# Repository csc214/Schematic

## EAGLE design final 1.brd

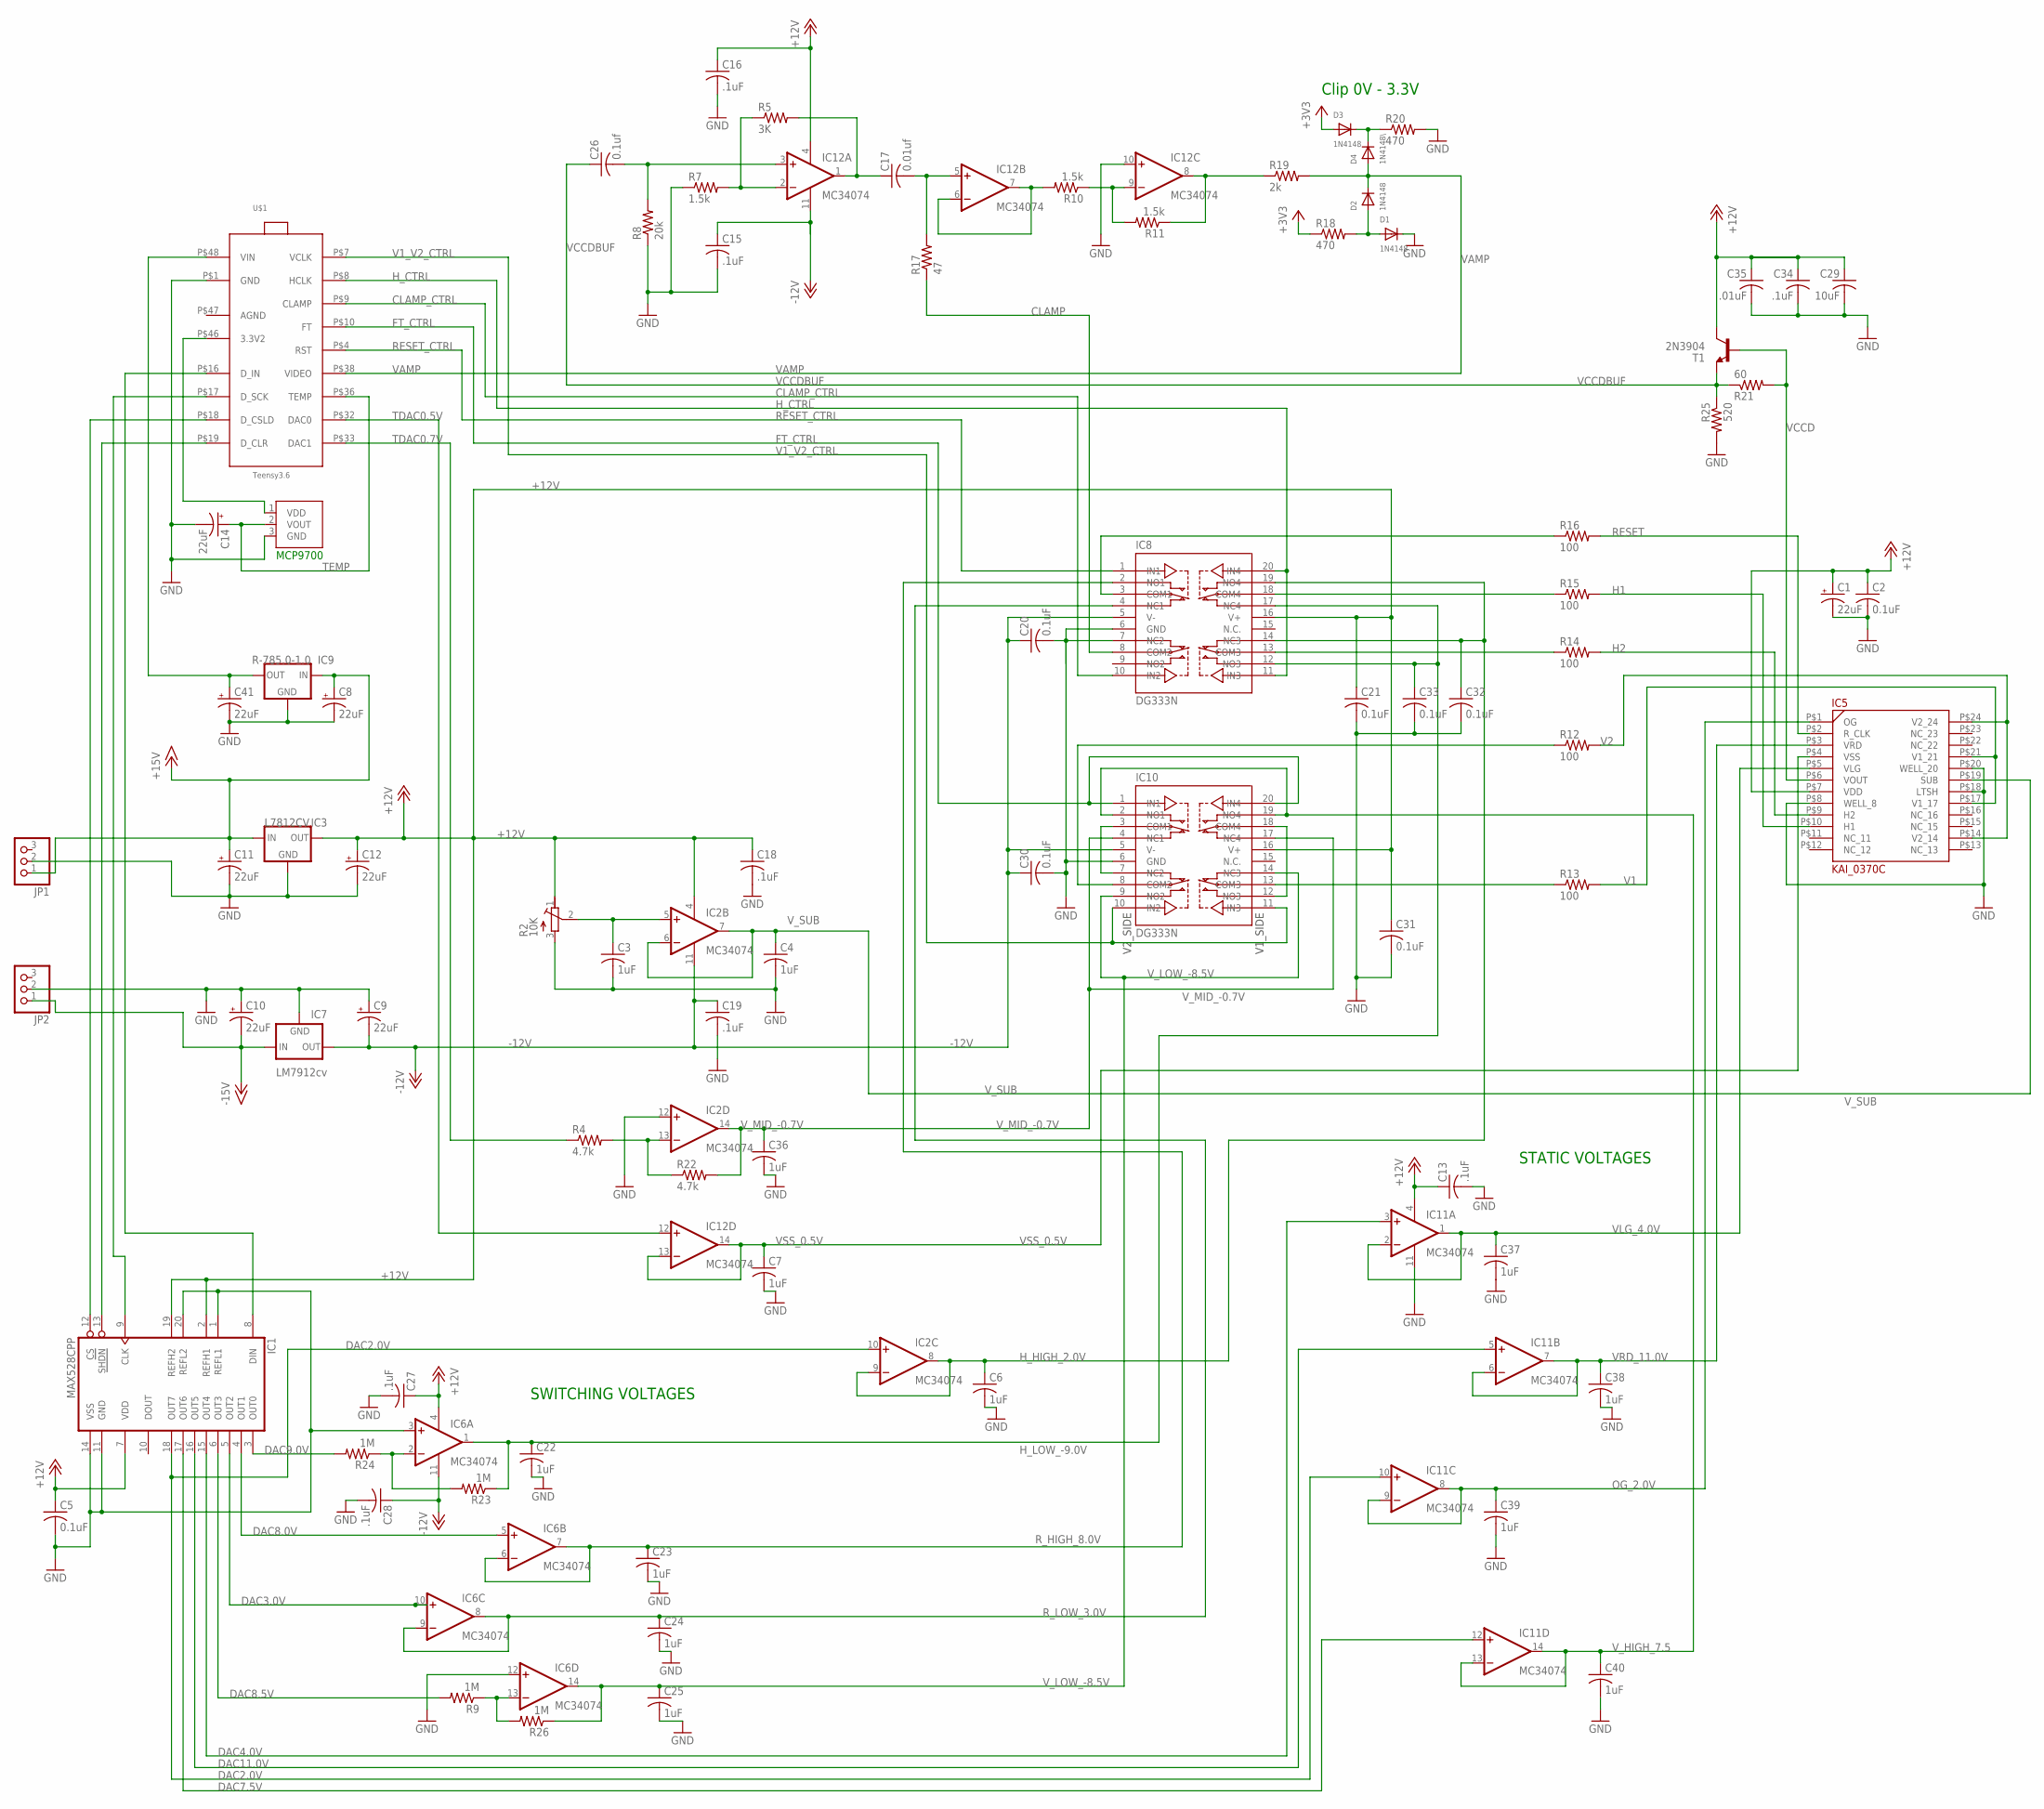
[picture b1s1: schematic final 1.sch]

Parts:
C1, C8, C9, C10, C11, C12, C14, C41: 22uF; SANYO-OSCON_F
C2, C5, C20, C21, C30, C31, C32, C33: 0.1uF; C050-050X075
C3, C4, C6, C7, C22, C23, C24, C25, C36, C37, C38, C39, C40: 1uF; C050-050X075
C13, C15, C16, C18, C19, C27, C28, C34: .1uF; C050-050X075
C17: 0.01uf; C050-050X075
C26: 0.1uf; C050-050X075
C29: 10uF; C050-050X075
C35: .01uF; C050-050X075
D1, D2, D3: 1N4148; DO-1N4148
D4: 1N4148\; DO-1N4148
IC1: MAX528CPP; DIL20
IC2, IC6, IC11, IC12: MC34074; DIL14
IC3: L7812CV; 78XXS
IC5: KAI_0370C; KAI-0370C
IC7: LM7912cv; 79XXS
IC8, IC10: DG333N; DIL20
IC9: R-785.0-1.0; SIP3
JP1, JP2: PINHD-1X3; 1X03
R2: 10K; RTRIM3006P
R4, R22: 4.7k; 0207/2V
R5: 3K; 0207/2V
R7, R10, R11: 1.5k; 0207/2V
R8: 20k; 0207/2V
R9, R23, R24, R26: 1M; 0207/2V
R12, R13, R14, R15, R16: 100; 0207/2V
R17: 47; 0207/2V
R18, R20: 470; 0207/2V
R19: 2k; 0207/2V
R21: 60; 0207/2V
R25: 520; 0207/2V
T1: 2N3904; TO92
U$1: TEENSY3.6LIMITED; DIL
U$2: MCP970XTO; TO92

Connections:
+3V3: D3.A, R18.1
+5V: C41.+, IC9.3 (OUT), U$1.P$48 (VIN)
+12V: C1.+, C2.1, C5.1, C12.+, C13.1, C16.1, C18.1, C21.1, C27.1, C29.1, C31.1, C34.1, C35.1, IC1.2 (REFH1), IC1.7 (VDD), IC1.19 (REFH2), IC2.4 (V+), IC3.OUT, IC5.P$7 (VDD), IC6.4 (V+), IC8.16 (V+), IC10.16 (V+), IC11.4 (V+), IC12.4 (V+), R2.1 (A), T1.1 (C)
+15V: C8.+, C11.+, IC3.IN, IC9.1 (IN), JP1.1
-12V: C9.-, C15.1, C19.1, C20.1, C28.1, C30.1, IC2.11 (V-), IC6.11 (V-), IC7.OUT, IC8.5 (V-), IC10.5 (V-), IC12.11 (V-)
-15V: C10.-, IC7.IN, JP2.1
AGND: U$1.P$47 (AGND)
CLAMP: IC8.8 (COM2), R17.1
CLAMP_CTRL: IC8.10 (IN2), U$1.P$9 (CLAMP)
DAC2.0V: IC1.18 (OUT7), IC2.10 (+IN), IC11.10 (+IN)
DAC3.0V: IC1.5 (OUT2), IC6.10 (+IN)
DAC4.0V: IC1.15 (OUT4), IC11.3 (+IN)
DAC7.5V: IC1.17 (OUT6), IC11.12 (+IN)
DAC8.0V: IC1.4 (OUT1), IC6.5 (+IN)
DAC8.5V: IC1.6 (OUT3), R9.2
DAC9.0V: IC1.3 (OUT0), R24.2
DAC11.0V: IC1.16 (OUT5), IC11.5 (+IN)
FT_CTRL: IC10.1 (IN1), IC10.20 (IN4), U$1.P$10 (FT)
GND: C1.-, C2.2, C3.2, C4.2, C5.2, C6.2, C7.2, C8.-, C9.+, C10.+, C11.-, C12.-, C13.2, C14.-, C15.2, C16.2, C18.2, C19.2, C20.2, C21.2, C22.2, C23.2, C24.2, C25.2, C27.2, C28.2, C29.2, C30.2, C31.2, C32.2, C33.2, C34.2, C35.2, C36.2, C37.2, C38.2, C39.2, C40.2, C41.-, D1.C, IC1.1 (REFL1), IC1.11 (GND), IC1.14 (VSS), IC1.20 (REFL2), IC2.12 (+IN), IC3.GND, IC5.P$8 (WELL_8), IC5.P$18 (LTSH), IC5.P$20 (WELL_20), IC6.3 (+IN), IC6.12 (+IN), IC7.GND, IC8.6 (GND), IC8.7 (NC2), IC9.2 (GND), IC10.6 (GND), IC11.11 (V-), IC12.10 (+IN), JP1.2, JP2.2, R2.3 (E), R7.1, R8.1, R20.2, R25.2, U$1.P$1 (GND), U$2.3 (GND)
H1: IC5.P$10 (H1), R15.2
H2: IC5.P$9 (H2), R14.2
H_CTRL: IC8.11 (IN3), IC8.20 (IN4), U$1.P$8 (HCLK)
H_HIGH_2.0V: C6.1, C32.1, IC2.8 (OUT), IC2.9 (-IN), IC8.14 (NC3), IC8.19 (NO4)
H_LOW_-9.0V: C22.1, C33.1, IC6.1 (OUT), IC8.12 (NO3), IC8.17 (NC4), R23.1
unnamed: U$1.P$46 (3.3V2), U$2.1 (VDD)
unnamed: IC10.3 (COM1), IC10.7 (NC2)
unnamed: IC10.8 (COM2), R12.1
unnamed: IC1.8 (DIN), U$1.P$16 (D_IN)
unnamed: C3.1, IC2.5 (+IN), R2.2 (S)
unnamed: C17.1, IC12.1 (OUT), R5.2
unnamed: IC10.12 (NO3), IC10.18 (COM4)
unnamed: IC1.9 (CLK), U$1.P$17 (D_SCK)
unnamed: IC2.13 (-IN), R4.2, R22.1
unnamed: IC12.2 (-IN), R5.1, R7.2
unnamed: IC1.12 (CS), U$1.P$18 (D_CSLD)
unnamed: IC1.13 (SHDN), U$1.P$19 (D_CLR)
unnamed: IC12.8 (OUT), R11.1, R19.1
unnamed: IC8.13 (COM3), R14.1
unnamed: IC6.2 (-IN), R23.2, R24.1
unnamed: IC8.18 (COM4), R15.1
unnamed: IC12.6 (-IN), IC12.7 (OUT), R10.2
unnamed: IC5.P$2 (R_CLK), R16.2
unnamed: IC12.9 (-IN), R10.1, R11.2
unnamed: C26.2, IC12.3 (+IN), R8.2
unnamed: D1.A, D2.A, R18.2
unnamed: D3.C, D4.C, R20.1
unnamed: C17.2, IC12.5 (+IN), R17.2
unnamed: IC6.13 (-IN), R9.1, R26.2
OG_2.0V: C39.1, IC5.P$1 (OG), IC11.8 (OUT), IC11.9 (-IN)
RESET: IC8.3 (COM1), R16.1
RESET_CTRL: IC8.1 (IN1), U$1.P$4 (RST)
R_HIGH_8.0V: C23.1, IC6.6 (-IN), IC6.7 (OUT), IC8.2 (NO1)
R_LOW_3.0V: C24.1, IC6.8 (OUT), IC6.9 (-IN), IC8.4 (NC1)
TDAC0.5V: IC12.12 (+IN), U$1.P$32 (DAC0)
TDAC0.7V: R4.1, U$1.P$33 (DAC1)
TEMP: C14.+, U$1.P$36 (TEMP), U$2.2 (VOUT)
V1: IC5.P$17 (V1_17), IC5.P$21 (V1_21), R13.2
V1_V2_CTRL: IC10.10 (IN2), IC10.11 (IN3), U$1.P$7 (VCLK)
V2: IC5.P$14 (V2_14), IC5.P$24 (V2_24), R12.2
VAMP: D2.C, D4.A, R19.2, U$1.P$38 (VIDEO)
VCCD: IC5.P$6 (VOUT), R21.2, T1.2 (B)
VCCDBUF: C26.1, R21.1, R25.1, T1.3 (E)
VLG_4.0V: C37.1, IC5.P$5 (VLG), IC11.1 (OUT), IC11.2 (-IN)
VRD_11.0V: C38.1, IC5.P$3 (VRD), IC11.6 (-IN), IC11.7 (OUT)
VSS_0.5V: C7.1, IC5.P$4 (VSS), IC12.13 (-IN), IC12.14 (OUT)
V_2: IC10.13 (COM3), R13.1
V_HIGH_7.5: C40.1, IC10.2 (NO1), IC10.19 (NO4), IC11.13 (-IN), IC11.14 (OUT)
V_LOW_-8.5V: C25.1, IC6.14 (OUT), IC10.9 (NO2), IC10.14 (NC3), R26.1
V_MID_-0.7V: C36.1, IC2.14 (OUT), IC10.4 (NC1), IC10.17 (NC4), R22.2
V_SUB: C4.1, IC2.6 (-IN), IC2.7 (OUT), IC5.P$19 (SUB)

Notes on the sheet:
V2_SIDE
V1_SIDE
MCP9700
STATIC VOLTAGES
SWITCHING VOLTAGES
Clip 0V - 3.3V

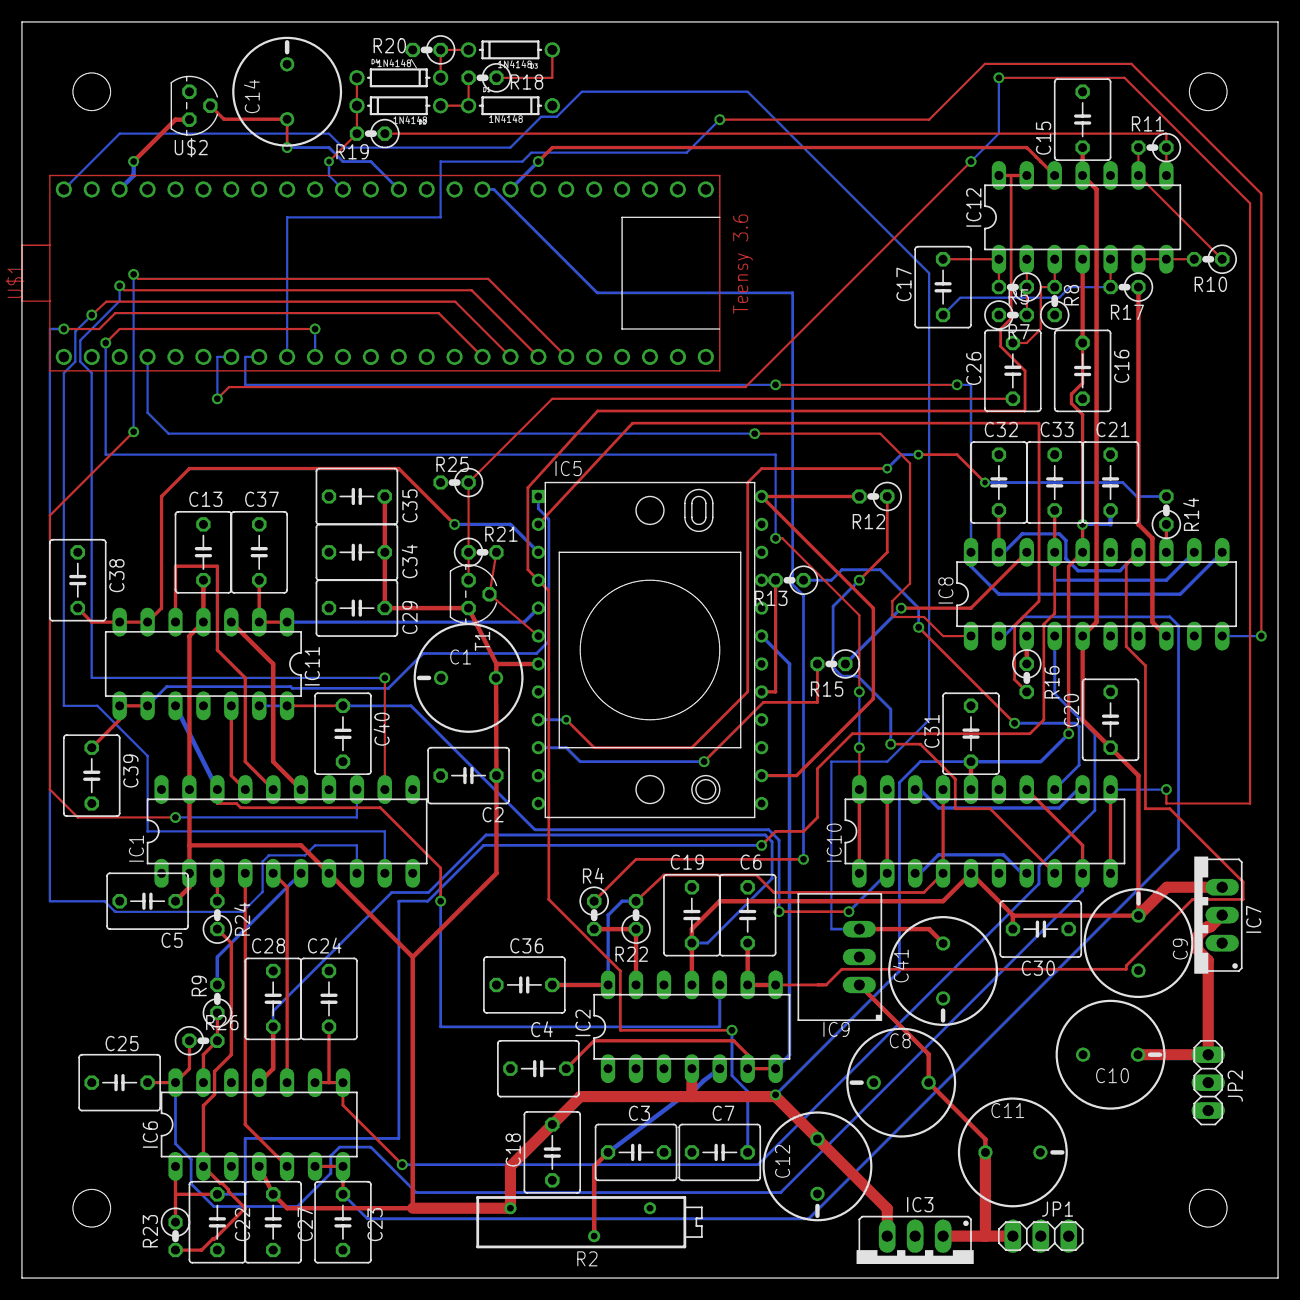
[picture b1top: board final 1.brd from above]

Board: 2 copper layers, 114.3 x 114.3 mm, 84 parts (0 on the bottom side), 69 nets.

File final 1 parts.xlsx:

ü | Part | Value | Device | Package | Description
 | D1 | 1N4148 | DIODEDO-1N4148 | DO-1N4148 | Diode
 | D2 | 1N4148 | DIODEDO-1N4148 | DO-1N4148 | Diode
 | D3 | 1N4148 | DIODEDO-1N4148 | DO-1N4148 | Diode
 | D4 | 1N4148 | DIODEDO-1N4148 | DO-1N4148 | Diode
 | R4 | 4.7k | R-US_0207/2V | 0207/2V | RESISTOR, American symbol
 | R5 | 3K | R-US_0207/2V | 0207/2V | RESISTOR, American symbol
 | R7 | 1.5k | R-US_0207/2V | 0207/2V | RESISTOR, American symbol
 | R8 | 20k | R-US_0207/2V | 0207/2V | RESISTOR, American symbol
 | R9 | 1M | R-US_0207/2V | 0207/2V | RESISTOR, American symbol
 | R10 | 1.5k | R-US_0207/2V | 0207/2V | RESISTOR, American symbol
 | R11 | 1.5k | R-US_0207/2V | 0207/2V | RESISTOR, American symbol
 | R12 | 100 | R-US_0207/2V | 0207/2V | RESISTOR, American symbol
 | R13 | 100 | R-US_0207/2V | 0207/2V | RESISTOR, American symbol
 | R14 | 100 | R-US_0207/2V | 0207/2V | RESISTOR, American symbol
 | R15 | 100 | R-US_0207/2V | 0207/2V | RESISTOR, American symbol
 | R16 | 100 | R-US_0207/2V | 0207/2V | RESISTOR, American symbol
 | R17 | 47 | R-US_0207/2V | 0207/2V | RESISTOR, American symbol
 | R18 | 470 | R-US_0207/2V | 0207/2V | RESISTOR, American symbol
 | R19 | 2k | R-US_0207/2V | 0207/2V | RESISTOR, American symbol
 | R20 | 470 | R-US_0207/2V | 0207/2V | RESISTOR, American symbol
 | R21 | 60 | R-US_0207/2V | 0207/2V | RESISTOR, American symbol
 | R22 | 4.7k | R-US_0207/2V | 0207/2V | RESISTOR, American symbol
 | R23 | 1M | R-US_0207/2V | 0207/2V | RESISTOR, American symbol
 | R24 | 1M | R-US_0207/2V | 0207/2V | RESISTOR, American symbol
 | R25 | 520 | R-US_0207/2V | 0207/2V | RESISTOR, American symbol
 | R26 | 1M | R-US_0207/2V | 0207/2V | RESISTOR, American symbol
 | C1 | 22uF | CPOL-USSANYO_F | SANYO-OSCON_F | POLARIZED CAPACITOR, American symbol
 | C2 | 0.1uF | C-US050-050X075 | C050-050X075 | CAPACITOR, American symbol
 | C3 | 1uF | C-US050-050X075 | C050-050X075 | CAPACITOR, American symbol
 | C4 | 1uF | C-US050-050X075 | C050-050X075 | CAPACITOR, American symbol
 | C5 | 0.1uF | C-US050-050X075 | C050-050X075 | CAPACITOR, American symbol
 | C6 | 1uF | C-US050-050X075 | C050-050X075 | CAPACITOR, American symbol
 | C7 | 1uF | C-US050-050X075 | C050-050X075 | CAPACITOR, American symbol
 | C8 | 22uF | CPOL-USSANYO_F | SANYO-OSCON_F | POLARIZED CAPACITOR, American symbol
 | C9 | 22uF | CPOL-USSANYO_F | SANYO-OSCON_F | POLARIZED CAPACITOR, American symbol
 | C10 | 22uF | CPOL-USSANYO_F | SANYO-OSCON_F | POLARIZED CAPACITOR, American symbol
 | C11 | 22uF | CPOL-USSANYO_F | SANYO-OSCON_F | POLARIZED CAPACITOR, American symbol
 | C12 | 22uF | CPOL-USSANYO_F | SANYO-OSCON_F | POLARIZED CAPACITOR, American symbol
 | C13 | .1uF | C-US050-050X075 | C050-050X075 | CAPACITOR, American symbol
 | C14 | 22uF | CPOL-USSANYO_F | SANYO-OSCON_F | POLARIZED CAPACITOR, American symbol
 | C15 | .1uF | C-US050-050X075 | C050-050X075 | CAPACITOR, American symbol
 | C16 | .1uF | C-US050-050X075 | C050-050X075 | CAPACITOR, American symbol
 | C17 | 0.01uf | C-US050-050X075 | C050-050X075 | CAPACITOR, American symbol
 | C18 | .1uF | C-US050-050X075 | C050-050X075 | CAPACITOR, American symbol
 | C19 | .1uF | C-US050-050X075 | C050-050X075 | CAPACITOR, American symbol
 | C20 | 0.1uF | C-US050-050X075 | C050-050X075 | CAPACITOR, American symbol
 | C21 | 0.1uF | C-US050-050X075 | C050-050X075 | CAPACITOR, American symbol
 | C22 | 1uF | C-US050-050X075 | C050-050X075 | CAPACITOR, American symbol
 | C23 | 1uF | C-US050-050X075 | C050-050X075 | CAPACITOR, American symbol
 | C24 | 1uF | C-US050-050X075 | C050-050X075 | CAPACITOR, American symbol
 | C25 | 1uF | C-US050-050X075 | C050-050X075 | CAPACITOR, American symbol
 | C26 | 0.1uf | C-US050-050X075 | C050-050X075 | CAPACITOR, American symbol
 | C27 | .1uF | C-US050-050X075 | C050-050X075 | CAPACITOR, American symbol
 | C28 | .1uF | C-US050-050X075 | C050-050X075 | CAPACITOR, American symbol
 | C29 | 10uF | C-US050-050X075 | C050-050X075 | CAPACITOR, American symbol
 | C30 | 0.1uF | C-US050-050X075 | C050-050X075 | CAPACITOR, American symbol
 | C31 | 0.1uF | C-US050-050X075 | C050-050X075 | CAPACITOR, American symbol
 | C32 | 0.1uF | C-US050-050X075 | C050-050X075 | CAPACITOR, American symbol
 | C33 | 0.1uF | C-US050-050X075 | C050-050X075 | CAPACITOR, American symbol
 | C34 | .1uF | C-US050-050X075 | C050-050X075 | CAPACITOR, American symbol
 | C35 | .01uF | C-US050-050X075 | C050-050X075 | CAPACITOR, American symbol
 | C36 | 1uF | C-US050-050X075 | C050-050X075 | CAPACITOR, American symbol
 | C37 | 1uF | C-US050-050X075 | C050-050X075 | CAPACITOR, American symbol
 | C38 | 1uF | C-US050-050X075 | C050-050X075 | CAPACITOR, American symbol
 | C39 | 1uF | C-US050-050X075 | C050-050X075 | CAPACITOR, American symbol
 | C40 | 1uF | C-US050-050X075 | C050-050X075 | CAPACITOR, American symbol
 | C41 | 22uF | CPOL-USSANYO_F | SANYO-OSCON_F | POLARIZED CAPACITOR, American symbol
 | JP1 |  | PINHD-1X3 | 1X03 | PIN HEADER
 | JP2 |  | PINHD-1X3 | 1X03 | PIN HEADER
 | R2 | 10K | R-TRIMM3006P | RTRIM3006P | Trimm resistor
 | T1 | 2N3904 | 2N3904 | TO92 | NPN TRANSISTOR
 | U$2 | MCP970XTO | MCP970XTO | TO92
 | IC1 | MAX528CPP | MAX528CPP | DIL20 | DIGITAL/ANALOG CONVERTER
 | IC2 | MC34074 | LM324N | DIL14 | OP AMP
 | IC6 | MC34074 | LM324N | DIL14 | OP AMP
 | IC11 | MC34074 | LM324N | DIL14 | OP AMP
 | IC12 | MC34074 | LM324N | DIL14 | OP AMP
 | IC3 | L7812CV | 78XXS | 78XXS | VOLTAGE REGULATOR
 | IC7 | LM7912cv | 79XXS | 79XXS | VOLTAGE REGULATOR
 | IC9 | R-785.0-1.0 | R-785.0-1.0 | SIP3 | Innoline R-78xx-1.0 Series Switching Regulators - 1.0A, Standard
 | IC8 | DG333N | MAX333N | DIL20
 | IC10 | DG333N | MAX333N | DIL20
 | IC5 | KAI_0370C | KAI_0370C | KAI-0370C
 | U$1 | TEENSY3.6LIMITED | TEENSY3.6LIMITED | DIL

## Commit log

2017-05-24 First commit (All credit to Max, Justin, and Venable.)

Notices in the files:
parts and their libraries:
r-78xx_10: (c) 2015 Samuel Lourenço
